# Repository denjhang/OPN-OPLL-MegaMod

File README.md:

# OPN-OPLL-MegaMod
 OPN+OPLL MegaMod, the latest hardware version has passed hardware verification
 
# 2023.11.25
OPN+OPLL MegaMod v0.3 have passed hardware testing and all functions have been verified. The old version has many problems and is not recommended.  
## OPN+OPLL MegaMod v0.3 includes the following features:
1. OPN and OPLL chips can support playing VGM music of PC-9801-26K, MSX-Music, ZX-Spectrum, and Atari ST. Software driver support provided by natalie.  
2. A typical dual op amp driven by a single 5V (take NE5532 as an example), it works well and sounds loud. It is especially effective for the sound amplification function of OPLL.  
3. Independent volume adjustment knob. Supports adjusting the volume of OPN and SSG, as well as the overall volume of the mixer. The volume of OPLL cannot be adjusted because the volume of OPLL itself is too small. This function is completely normal, and the volumes of each channel will not interfere with each other when adjusting the volume.  
4. SSG can be configured with stereo sound. Use three three-position toggle switches to independently control the stereo channels of each SSG. This function is completely normal and will not affect the volume of OPN and OPLL.
5. SSG stereo mixing circuit. This part is based on the ZX-Spectrum's golden ratio mixing circuit, but I modified the resistor values to provide a more stereo effect.  
6. OPN and OPLL monophonic mixing circuit. Since there is no such combination of using OPN.FM+OPLL at the same time, OPN and OPLL configurable stereo make little sense. A mono mix is used here, which means the left and right channels sound the same.  
7. Compatible with OPLL cloning chip. Just remove the pull-down resistors of the MO and RO analog audio tree pool of YM2413.  
8. Compatible with U3567, UM3567, YM2413-F and YM2413B-F, using a simple conversion board to implement.

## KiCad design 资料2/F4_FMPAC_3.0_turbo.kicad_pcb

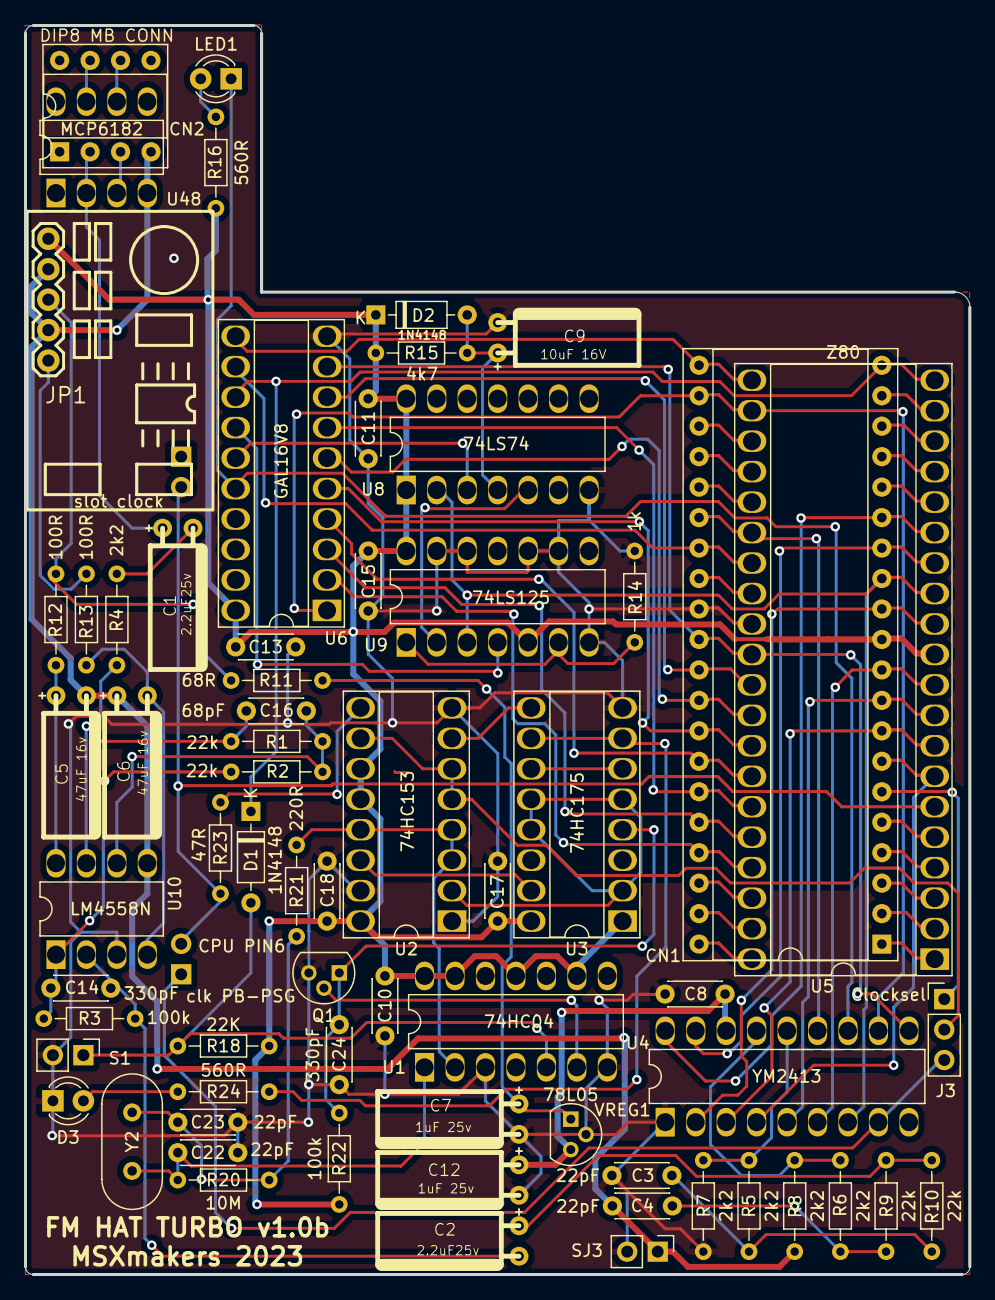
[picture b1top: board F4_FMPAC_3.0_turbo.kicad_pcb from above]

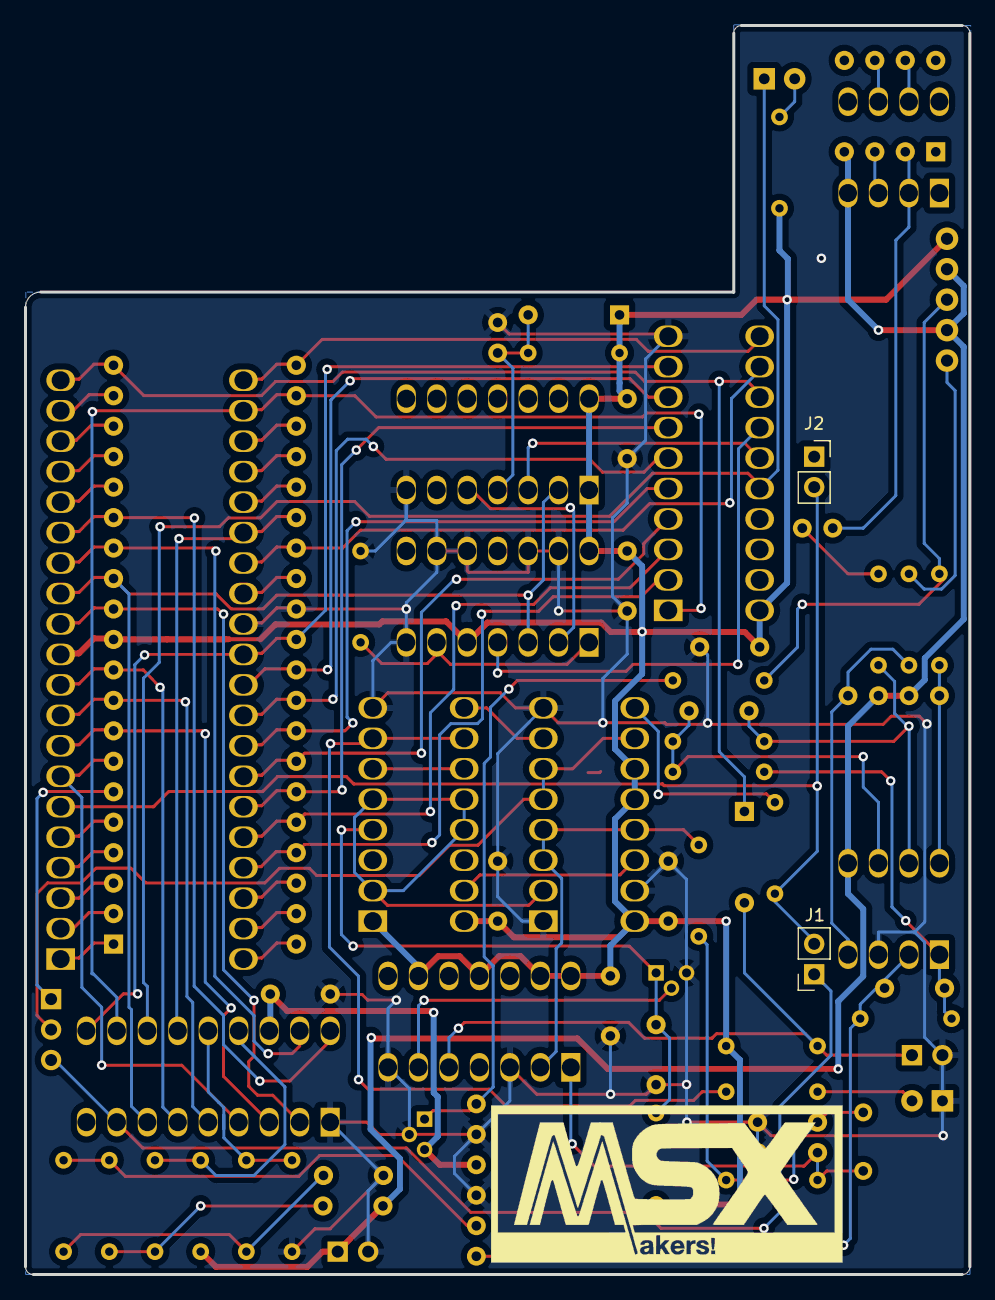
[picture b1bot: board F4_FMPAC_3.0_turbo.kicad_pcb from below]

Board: 2 copper layers, 78.7 x 104.1 mm, 68 parts (2 on the bottom side), 84 nets.

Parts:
C1, C2: 2.2uF25v; CP_tumbado
C3, C4, C22, C23: 22pF; C_Disc_D4.3mm_W1.9mm_P5.00mm
C5, C6: 47uF 16v; CP_tumbado
C7, C12: 1uF 25v; CP_tumbado
C8, C10, C11, C13, C15, C17, C18: 100nF; C_Disc_D4.3mm_W1.9mm_P5.00mm
C9: 10uF 16V; CP_tumbado
C14, C24: 330pF; C_Disc_D4.3mm_W1.9mm_P5.00mm
C16: 68pF; C_Disc_D4.3mm_W1.9mm_P5.00mm
CN1: DIP40 MB CONN; DIP-40_W15.24mm_Socket
CN2: DIP8 MB CONN; DIP-8_W7.62mm_Socket
D1, D2: 1N4148; D_DO-35_SOD27_P7.62mm_Horizontal
D3: LED; LED_D3.0mm
J1: clock_sel MB/JP; PinSocket_1x02_P2.54mm_Vertical
J2: slot clock; PinSocket_1x02_P2.54mm_Vertical
J3: Clocksel; PinHeader_1x03_P2.54mm_Vertical
JP1: Conn_01x05; Eletechsup_DD1718PA
LED1: LED 3mm; LED_D3.0mm
Q1: BS170; TO-92L
R1, R2, R9, R10: 22k; R_Axial_DIN0204_L3.6mm_D1.6mm_P7.62mm_Horizontal
R3, R22: 100k; R_Axial_DIN0204_L3.6mm_D1.6mm_P7.62mm_Horizontal
R4, R5, R6, R7, R8: 2k2; R_Axial_DIN0204_L3.6mm_D1.6mm_P7.62mm_Horizontal
R11: 68R; R_Axial_DIN0204_L3.6mm_D1.6mm_P7.62mm_Horizontal
R12, R13: 100R; R_Axial_DIN0204_L3.6mm_D1.6mm_P7.62mm_Horizontal
R14: 1k; R_Axial_DIN0204_L3.6mm_D1.6mm_P7.62mm_Horizontal
R15: 4k7; R_Axial_DIN0204_L3.6mm_D1.6mm_P7.62mm_Horizontal
R16, R24: 560R; R_Axial_DIN0204_L3.6mm_D1.6mm_P7.62mm_Horizontal
R18: 22K; R_Axial_DIN0204_L3.6mm_D1.6mm_P7.62mm_Horizontal
R20: 10M; R_Axial_DIN0204_L3.6mm_D1.6mm_P7.62mm_Horizontal
R21: 220R; R_Axial_DIN0204_L3.6mm_D1.6mm_P7.62mm_Horizontal
R23: 47R; R_Axial_DIN0204_L3.6mm_D1.6mm_P7.62mm_Horizontal
S1: turbo_on; PinHeader_1x02_P2.54mm_Vertical
SJ3: SJ; PinHeader_1x02_P2.54mm_Vertical
U1: 74HC04; DIP-14c_W7.62mm_LongPads
U2: 74HC153; DIP-16c_W7.62mm_Socket_LongPads
U3: 74HC175; DIP-16c_W7.62mm_Socket_LongPads
U4: YM2413; DIP-18c_W7.62mm_LongPads
U5: Z80; DIP-40c_W15.24mm_Socket_LongPads
U6: GAL16V8; DIP-20c_W7.62mm_Socket_LongPads
U8: 74LS74; DIP-14c_W7.62mm_LongPads
U9: 74LS125; DIP-14c_W7.62mm_LongPads
U10: LM4558N; DIP-8c_W7.62mm_LongPads
U48: MCP6182; DIP-8c_W7.62mm_LongPads
VREG1: 78L05; TO-92L
Y2: HighFreq; Crystal_HC49-U_Vertical

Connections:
+5V: C10.1, C11.1, C13.1, C15.1, C17.1, C18.1, CN1.11, D2.1 (K), JP1.1, R15.1, R16.2, R18.1, R22.1, U1.9, U1.11, U1.13, U1.14 (VCC), U2.11 (I1b), U2.12 (I2b), U2.16 (VCC), U3.1 (~Mr), U3.16 (VCC), U5.11 (VCC), U6.20 (VCC), U8.1 (~R), U8.14 (VCC), U9.5, U9.14 (VCC)
+12V: JP1.3, R11.2, R12.2
-12V: JP1.5, R13.2
/+5VREG: C8.2, C12.1, U4.16, VREG1.3 (OUT)
/A0: CN1.30, U4.10, U5.30 (A0), U6.9 (I9)
/A1: CN1.31, U5.31 (A1), U6.8 (I8)
/A2: CN1.32, U5.32 (A2), U6.6 (I6)
/A3: CN1.33, U5.33 (A3), U6.5 (I5)
/A4: CN1.34, U5.34 (A4), U6.4 (I4)
/A5: CN1.35, U5.35 (A5), U6.7 (I7)
/A6: CN1.36, U5.36 (A6), U6.3 (I3)
/A7: CN1.37, U5.37 (A7), U6.2 (I2)
/A8: CN1.38, U5.38 (A8)
/A9: CN1.39, U5.39 (A9)
/A10: CN1.40, U5.40 (A10)
/A11: CN1.1, U5.1 (A11)
/A12: CN1.2, U5.2 (A12)
/A13: CN1.3, U5.3 (A13)
/A14: CN1.4, U5.4 (A14)
/A15: CN1.5, U5.5 (A15)
/AMP: C1.1, CN2.2 (-), U48.2 (-)
/BUSAK: CN1.23, U5.23 (BUSAK)
/BUSRQ: CN1.25, U5.25 (BUSRQ)
/CLCK: J1.2, J2.2, R23.2, U5.6 (CLK)
/D0: CN1.14, U4.17, U5.14 (D0)
/D1: CN1.15, U4.18, U5.15 (D1)
/D2: CN1.12, U4.2, U5.12 (D2)
/D3: CN1.8, U4.3, U5.8 (D3)
/D4: CN1.7, U4.4, U5.7 (D4)
/D5: CN1.9, U4.5, U5.9 (D5)
/D6: CN1.10, U4.6, U5.10 (D6)
/D7: CN1.13, U4.7, U5.13 (D7), U8.2 (D), U9.3
/F4RD: U6.14 (IO6), U9.4
/F4WR: U6.15 (IO5), U8.3 (C)
/FMCS: LED1.1 (K), U4.12, U6.16 (IO4)
/HALT: CN1.18, U5.18 (HALT)
/INT: CN1.16, U5.16 (INT)
/IORQ: CN1.20, D1.1 (K), U5.20 (IORQ), U6.13 (IO7)
/M1: CN1.27, U5.27 (M1), U6.12 (IO8)
/MB_CLCK1: J1.1, J3.3, U4.8
/MB_CLCK2: CN1.6, J3.1
/MREQ: CN1.19, U5.19 (MREQ)
/NMI: CN1.17, U5.17 (NMI)
/RD: CN1.21, U5.21 (RD), U6.11 (I10/~OE)
/RFSH: CN1.28, U5.28 (RFSH)
/RST: CN1.26, U4.13, U5.26 (RESET)
/WAIT: CN1.24, U5.24 (WAIT)
/WR: CN1.22, U4.11, U5.22 (WR), U6.1 (I1/CLK)
GND: C3.1, C7.2, C8.1, C9.2, C10.2, C11.2, C12.2, C13.2, C15.2, C17.2, C18.2, C22.2, C23.2, C24.2, CN1.29, D3.1 (K), Q1.3 (S), R7.2, R14.1, S1.2, SJ3.2, U1.3, U1.7 (GND), U2.1 (Ea), U2.8 (GND), U2.15 (Eb), U3.8 (GND), U4.1, U5.29 (GND), U6.10 (GND), U8.7 (GND), U9.7 (GND), U9.9, U9.10, U9.12, U9.13, U10.3 (+IN), VREG1.2 (GND)
GND1: C4.2, C5.2, C6.1, CN2.4 (V-), JP1.2, JP1.4, R8.1, SJ3.1, U10.5 (+IN), U48.4 (V-)
unnamed: C1.2, R4.2
unnamed: C2.1, R9.2, R10.2
unnamed: C3.2, R5.2, R10.1
unnamed: C4.1, R6.2, R9.1
unnamed: C5.1, R12.1, U10.8 (V+)
unnamed: C6.2, R13.1, U10.4 (V-)
unnamed: C7.1, R11.1, VREG1.1 (IN)
unnamed: C9.1, D2.2 (A), R15.2, U8.4 (~S)
unnamed: C2.2, C14.1, R3.1, U10.2 (-IN)
unnamed: C14.2, R2.2, R3.2, U10.1 (OUT)
unnamed: C16.1, R1.1, R2.1, U10.6 (-IN)
unnamed: C16.2, R1.2, R4.1, U10.7 (OUT)
unnamed: C22.1, R20.1, U1.1, Y2.1
unnamed: C23.1, R20.2, R21.1, Y2.2
unnamed: C24.1, Q1.1 (D), R22.2, U3.4 (D0)
unnamed: CN2.3 (+), U48.3 (+)
unnamed: CN2.6, U48.6
unnamed: CN2.7 (V+), U48.7 (V+)
unnamed: D1.2 (A), R18.2, S1.1, U1.5
unnamed: D3.2 (A), R24.2
unnamed: J3.2, U2.5 (I1a), U2.6 (I0a), U2.10 (I0b)
unnamed: LED1.2 (A), R16.1
unnamed: Q1.2 (G), U1.6
unnamed: R5.1, R7.1, U4.14
unnamed: R6.1, R8.2, U4.15
unnamed: R14.2, U9.1, U9.6
unnamed: R21.2, U1.2, U2.3 (I3a), U2.4 (I2a), U2.13 (I3b)
unnamed: R23.1, U2.9 (Zb)
unnamed: R24.1, U3.7 (Q1), U3.10 (Q2)
unnamed: U2.2 (S1), U3.2 (Q0), U3.5 (D1), U3.12 (D2), U3.13 (D3)
unnamed: U2.7 (Za), U3.9 (Cp)
unnamed: U2.14 (S0), U3.15 (Q3)
unnamed: U3.6 (~Q1), U3.11 (~Q2)
unnamed: U8.5 (Q), U9.2

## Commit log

2023-12-11 new pics
